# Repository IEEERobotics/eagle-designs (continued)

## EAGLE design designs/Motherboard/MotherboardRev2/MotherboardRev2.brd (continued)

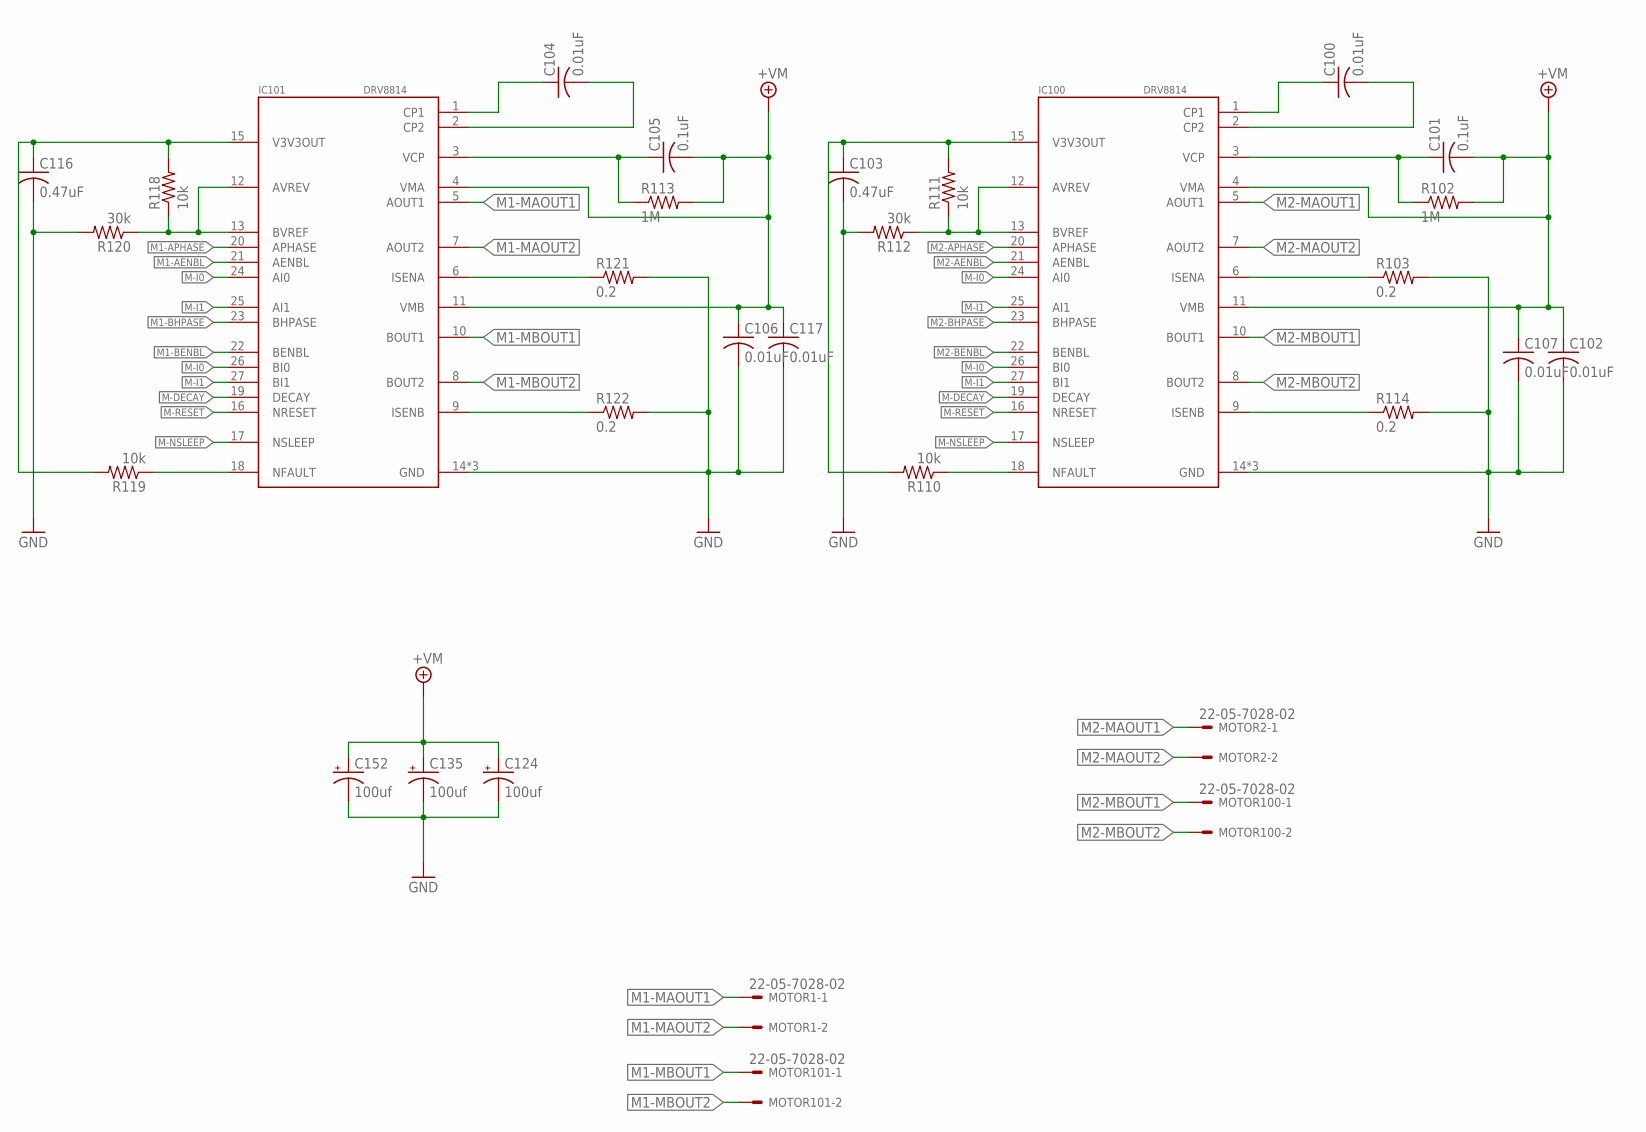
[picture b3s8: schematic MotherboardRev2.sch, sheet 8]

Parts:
C100, C102, C104, C106, C107, C117: 0.01uF; C0402
C101, C105: 0.1uF; C0402
C103, C116: 0.47uF; C0402
C124, C135, C152: 100uf; 153CLV-0605
IC100, IC101: DRV8814; TSSOP-28
MOTOR1, MOTOR2, MOTOR100, MOTOR101: 22-05-7028-02; 7395-02
R102, R113: 1M; R0402
R103, R114, R121, R122: 0.2; R0402
R110, R111, R118, R119: 10k; R0402
R112, R120: 30k; R0402

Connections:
+7V: C101.2, C102.1, C105.2, C106.1, C107.1, C117.1, C124.+, C135.+, C152.+, IC100.4 (VMA), IC100.11 (VMB), IC101.4 (VMA), IC101.11 (VMB), R102.2, R113.2; also elsewhere on the board
GND: C102.2, C103.2, C106.2, C107.2, C116.2, C117.2, C124.-, C135.-, C152.-, IC100.14 (GND), IC100.28 (GND), IC100.EXP (GND), IC101.14 (GND), IC101.28 (GND), IC101.EXP (GND), R103.2, R112.2, R114.2, R120.2, R121.2, R122.2; also elsewhere on the board
M1-AENBL: IC101.21 (AENBL); also elsewhere on the board
M1-APHASE: IC101.20 (APHASE); also elsewhere on the board
M1-BENBL: IC101.22 (BENBL); also elsewhere on the board
M1-BHPASE: IC101.23 (BHPASE); also elsewhere on the board
M1-MAOUT1: IC101.5 (AOUT1), MOTOR1.1
M1-MAOUT2: IC101.7 (AOUT2), MOTOR1.2
M1-MBOUT1: IC101.10 (BOUT1), MOTOR101.1
M1-MBOUT2: IC101.8 (BOUT2), MOTOR101.2
M2-AENBL: IC100.21 (AENBL); also elsewhere on the board
M2-APHASE: IC100.20 (APHASE); also elsewhere on the board
M2-BENBL: IC100.22 (BENBL); also elsewhere on the board
M2-BHPASE: IC100.23 (BHPASE); also elsewhere on the board
M2-MAOUT1: IC100.5 (AOUT1), MOTOR2.1
M2-MAOUT2: IC100.7 (AOUT2), MOTOR2.2
M2-MBOUT1: IC100.10 (BOUT1), MOTOR100.1
M2-MBOUT2: IC100.8 (BOUT2), MOTOR100.2
M-DECAY: IC100.19 (DECAY), IC101.19 (DECAY); also elsewhere on the board
M-I0: IC100.24 (AI0), IC100.26 (BI0), IC101.24 (AI0), IC101.26 (BI0); also elsewhere on the board
M-I1: IC100.25 (AI1), IC100.27 (BI1), IC101.25 (AI1), IC101.27 (BI1); also elsewhere on the board
M-NSLEEP: IC100.17 (NSLEEP), IC101.17 (NSLEEP); also elsewhere on the board
M-RESET: IC100.16 (NRESET), IC101.16 (NRESET); also elsewhere on the board
unnamed: C104.2, IC101.2 (CP2)
unnamed: C104.1, IC101.1 (CP1)
unnamed: C105.1, IC101.3 (VCP), R113.1
unnamed: IC101.6 (ISENA), R121.1
unnamed: IC101.9 (ISENB), R122.1
unnamed: IC101.12 (AVREV), IC101.13 (BVREF), R118.1, R120.1
unnamed: C100.2, IC100.2 (CP2)
unnamed: C100.1, IC100.1 (CP1)
unnamed: C101.1, IC100.3 (VCP), R102.1
unnamed: IC100.6 (ISENA), R103.1
unnamed: IC100.9 (ISENB), R114.1
unnamed: IC100.12 (AVREV), IC100.13 (BVREF), R111.1, R112.1
unnamed: IC101.18 (NFAULT), R119.1
unnamed: C116.1, IC101.15 (V3V3OUT), R118.2, R119.2
unnamed: IC100.18 (NFAULT), R110.1
unnamed: C103.1, IC100.15 (V3V3OUT), R110.2, R111.2

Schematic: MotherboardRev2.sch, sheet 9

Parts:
C119, C123, C131, C138, C142, C147, C150: 0.1uF; C0402
C120, C121, C122, C139, C140, C141: 0.22uF; C0402
C132, C133, C148, C149: 1nF; C0402
C134: .1uF; C0402
R125, R132, R137, R139: 0.1; R0402
R126, R127, R140, R141: 47k; R0402
R128, R129, R130, R131, R142, R143, R144, R145: 10k; R0402
STEP1, STEP2: 22-05-7048-04; 7395-04
U100, U102: DRV8811PWP; SOP65P640X120-29N

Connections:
3.3V: C131.1, C147.1, R130.1, R131.1, R142.1, R144.1, U100.10 (VCC), U102.10 (VCC); also elsewhere on the board
+7V: C119.1, C121.1, C123.1, C138.1, C140.1, C142.1, U100.15 (VMB), U100.28 (VMA), U102.15 (VMB), U102.28 (VMA); also elsewhere on the board
GND: C119.2, C120.2, C123.2, C131.2, C132.2, C133.2, C134.2, C138.2, C139.2, C142.2, C147.2, C148.2, C149.2, C150.2, R125.2, R126.2, R127.2, R128.2, R129.2, R132.2, R137.2, R139.2, R140.2, R141.2, R143.2, R145.2, U100.7 (GND_2), U100.21 (GND), U100.29 (EP), U102.7 (GND_2), U102.21 (GND), U102.29 (EP); also elsewhere on the board
M-NSLEEP: U100.27 (SLEEPN), U102.27 (SLEEPN); also elsewhere on the board
M-RESET: U100.17 (RESETN), U102.17 (RESETN); also elsewhere on the board
unnamed: R139.1, U102.14 (ISENB)
unnamed: R137.1, U102.1 (ISENA)
unnamed: C149.1, R141.1, U102.6 (RCA)
unnamed: C148.1, R140.1, U102.9 (RCB)
unnamed: C150.1, R144.2, R145.1, U102.5 (DECAY)
unnamed: R142.2, R143.1, U102.8 (VREF)
unnamed: C141.1, U102.23 (CP1)
unnamed: C141.2, U102.24 (CP2)
unnamed: C139.1, U102.20 (VGD)
unnamed: C140.2, U102.22 (VCP)
unnamed: R125.1, U100.14 (ISENB)
unnamed: R132.1, U100.1 (ISENA)
unnamed: C133.1, R127.1, U100.6 (RCA)
unnamed: C132.1, R126.1, U100.9 (RCB)
unnamed: C134.1, R129.1, R131.2, U100.5 (DECAY)
unnamed: R128.1, R130.2, U100.8 (VREF)
unnamed: C122.1, U100.23 (CP1)
unnamed: C122.2, U100.24 (CP2)
unnamed: C120.1, U100.20 (VGD)
unnamed: C121.2, U100.22 (VCP)
S1-AOUT1: STEP1.4, U102.4 (AOUT1)
S1-AOUT2: STEP1.1, U102.25 (AOUT2)
S1-BOUT1: STEP1.3, U102.11 (BOUT1)
S1-BOUT2: STEP1.2, U102.18 (BOUT2)
S1-DIR: U102.3 (DIR); also elsewhere on the board
S1-ENABLEN: U102.26 (ENABLEN); also elsewhere on the board
S1-HOME: U102.2 (HOME); also elsewhere on the board
S1-STEP: U102.19 (STEP); also elsewhere on the board
S2-AOUT1: STEP2.4, U100.4 (AOUT1)
S2-AOUT2: STEP2.1, U100.25 (AOUT2)
S2-BOUT1: STEP2.3, U100.11 (BOUT1)
S2-BOUT2: STEP2.2, U100.18 (BOUT2)
S2-DIR: U100.3 (DIR); also elsewhere on the board
S2-ENABLEN: U100.26 (ENABLEN); also elsewhere on the board
S2-HOME: U100.2 (HOME); also elsewhere on the board
S2-STEP: U100.19 (STEP); also elsewhere on the board
S-SRN: U100.16 (SRN), U102.16 (SRN); also elsewhere on the board
USM0: U100.13 (USM0), U102.13 (USM0); also elsewhere on the board
USM1: U100.12 (USM1), U102.12 (USM1); also elsewhere on the board

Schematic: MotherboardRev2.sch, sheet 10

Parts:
C1, C2, C4: 0.1uF; C0402
C3: 1uF; C0402
C19: 10uF; C0805
C115: .1uF; C0402
H1, H3: MOUNT-PAD-ROUND3.0; 3,0-PAD
IC103: PIC24FJ256GB106; TQFP64-10X10
MOTIN100, MOTIN101, MOTIN102, MOTIN103, MOTIN104: 22-05-7048-04; 7395-04
PROGRAMMING100: Jtag; MOTHER-BOARD-REV5_10-PIN-SMD
PWR_IN(2): 555X-2H; 5569-2
R116: 100; R0402
R117: 10k; R0402
SERVO_100, SERVO_101, SERVO_102: 22-05-7038-03; 7395-03
U$103: Switch3; MC32882_FINAL

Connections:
3.3V: C1.1, C2.1, C3.1, C4.1, IC103.10 (VDD), IC103.19 (AVDD), IC103.26 (VDD), IC103.38 (VDD), PROGRAMMING100.1, PROGRAMMING100.2, R117.2; also elsewhere on the board
+7V: C19.1, H1.B3,0, MOTIN100.2, MOTIN101.2, MOTIN101.3, MOTIN102.2, MOTIN103.2, MOTIN104.2, SERVO_100.2, SERVO_101.2, SERVO_102.2; also elsewhere on the board
CHANNEL_A_1: IC103.4 (RG6), MOTIN100.4
CHANNEL_A_2: IC103.22 (RB9), MOTIN102.3
CHANNEL_A_3: IC103.18 (RB7), MOTIN103.3
CHANNEL_A_4: IC103.8 (RG9), MOTIN104.3
CHANNEL_B_1: IC103.5 (RG7), MOTIN100.3
CHANNEL_B_2: IC103.21 (RB8), MOTIN102.4
CHANNEL_B_3: IC103.17 (RB6), MOTIN103.4
CHANNEL_B_4: IC103.6 (RG8), MOTIN104.4
GND: C1.2, C2.2, C3.2, C4.2, C19.2, C115.2, IC103.9 (VSS), IC103.20 (AVSS), IC103.25 (VSS), IC103.41 (VSS), MOTIN100.1, MOTIN101.1, MOTIN101.4, MOTIN102.1, MOTIN103.1, MOTIN104.1, PROGRAMMING100.9, PROGRAMMING100.10, PWR_IN(2).1, SERVO_100.3, SERVO_101.3, SERVO_102.3, U$103.P$1 (P1), U$103.P$4 (P4); also elsewhere on the board
M1-AENBL: IC103.47 (RC13); also elsewhere on the board
M1-APHASE: IC103.48 (RC14); also elsewhere on the board
M1-BENBL: IC103.46 (RD0); also elsewhere on the board
M1-BHPASE: IC103.45 (RD11); also elsewhere on the board
M2-AENBL: IC103.39 (RC12); also elsewhere on the board
M2-APHASE: IC103.43 (RD9); also elsewhere on the board
M2-BENBL: IC103.37 (RG2); also elsewhere on the board
M2-BHPASE: IC103.42 (RD8); also elsewhere on the board
M-DECAY: IC103.49 (RD1); also elsewhere on the board
M-I0: IC103.44 (RD10); also elsewhere on the board
M-I1: IC103.40 (RC15); also elsewhere on the board
M-NSLEEP: IC103.58 (RF0); also elsewhere on the board
M-RESET: IC103.60 (RE0); also elsewhere on the board
M_MCLR: C115.1, PROGRAMMING100.7, PROGRAMMING100.8, R116.2, R117.1, U$103.P$2 (P2), U$103.P$3 (P3)
M_MCLR': IC103.7 (!MCLR), R116.1
M_PGC1: IC103.15 (RB1), PROGRAMMING100.3, PROGRAMMING100.4
M_PGD1: IC103.16 (RB0), PROGRAMMING100.5, PROGRAMMING100.6
OC1': IC103.33 (RF3), SERVO_102.1
OC2': IC103.32 (RF5), SERVO_101.1
OC3': IC103.31 (RF4), SERVO_100.1
S1-DIR: IC103.64 (RE4); also elsewhere on the board
S1-ENABLEN: IC103.55 (RD7); also elsewhere on the board
S1-HOME: IC103.63 (RE3); also elsewhere on the board
S1-STEP: IC103.53 (RD5); also elsewhere on the board
S2-DIR: IC103.54 (RD6); also elsewhere on the board
S2-ENABLEN: IC103.51 (RD3); also elsewhere on the board
S2-HOME: IC103.52 (RD4); also elsewhere on the board
S2-STEP: IC103.50 (RD2); also elsewhere on the board
S-SRN: IC103.59 (RF1); also elsewhere on the board
SCL: IC103.2 (RE6); also elsewhere on the board
SDA: IC103.3 (RE7); also elsewhere on the board
USM0: IC103.62 (RE2); also elsewhere on the board
USM1: IC103.61 (RE1); also elsewhere on the board
VCC: PWR_IN(2).2; also elsewhere on the board
VDDCORE: IC103.56 (VDDCORE)

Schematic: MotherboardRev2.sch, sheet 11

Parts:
C6, C7, C8, C130: 4.7uF; 1206
C118: 10nF; 0805
C146: 330uF; SM_RADIAL_10AMM
D103: PDS760-13; POWERDI5
L103: WE-HCC-7443331000_1090; WE-HCC_1090
LED1, LED104: LEDCHIP-LED0603; CHIP-LED0603
POWER_ON: LEDCHIP-LED0603; CHIP-LED0603
R2, R101, R123, R146: 10k; R0402
R124: 2.55k; R0402
U$1: LOGO
U$107: TPS5450DDAR; R-PDSO-G8

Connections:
+7V: C146.1 (+), L103.2, R2.2, R123.2, R146.2; also elsewhere on the board
BOOT_VM: C118.1, U$107.1 (BOOT)
GND: C6.1, C7.1, C8.1, C130.1, C146.2 (-), D103.1 (A_2), LED1.C, LED104.C, POWER_ON.C, R124.1, U$107.6 (GND_2), U$107.9 (PWPD); also elsewhere on the board
unnamed: LED104.A, R146.1
unnamed: POWER_ON.A, R101.1
unnamed: LED1.A, R2.1
PH_VM: C118.2, D103.3 (K), L103.1, U$107.8 (PH)
VCC: C6.2, C7.2, C8.2, C130.2, R101.2, U$107.7 (VIN); also elsewhere on the board
VSNS_VM: R123.1, R124.2, U$107.4 (VSNS)

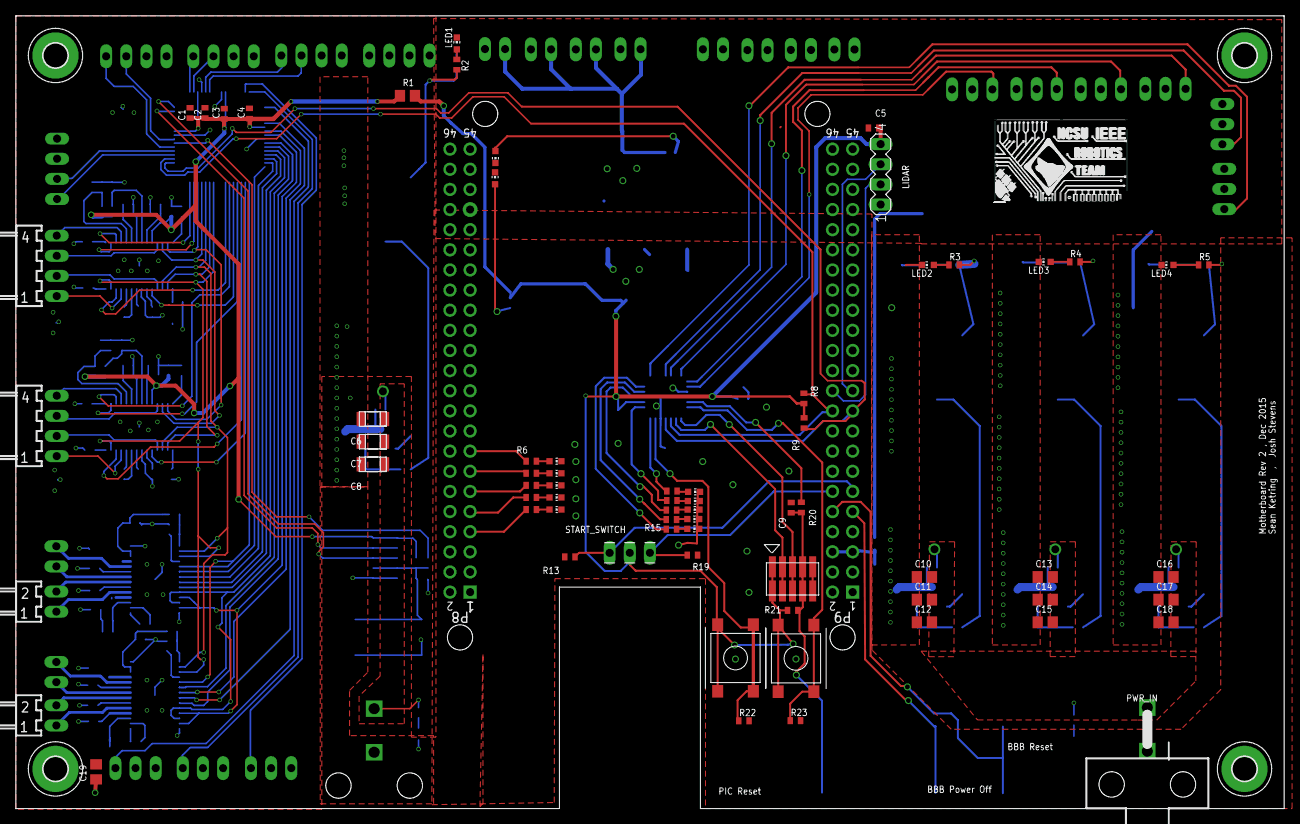
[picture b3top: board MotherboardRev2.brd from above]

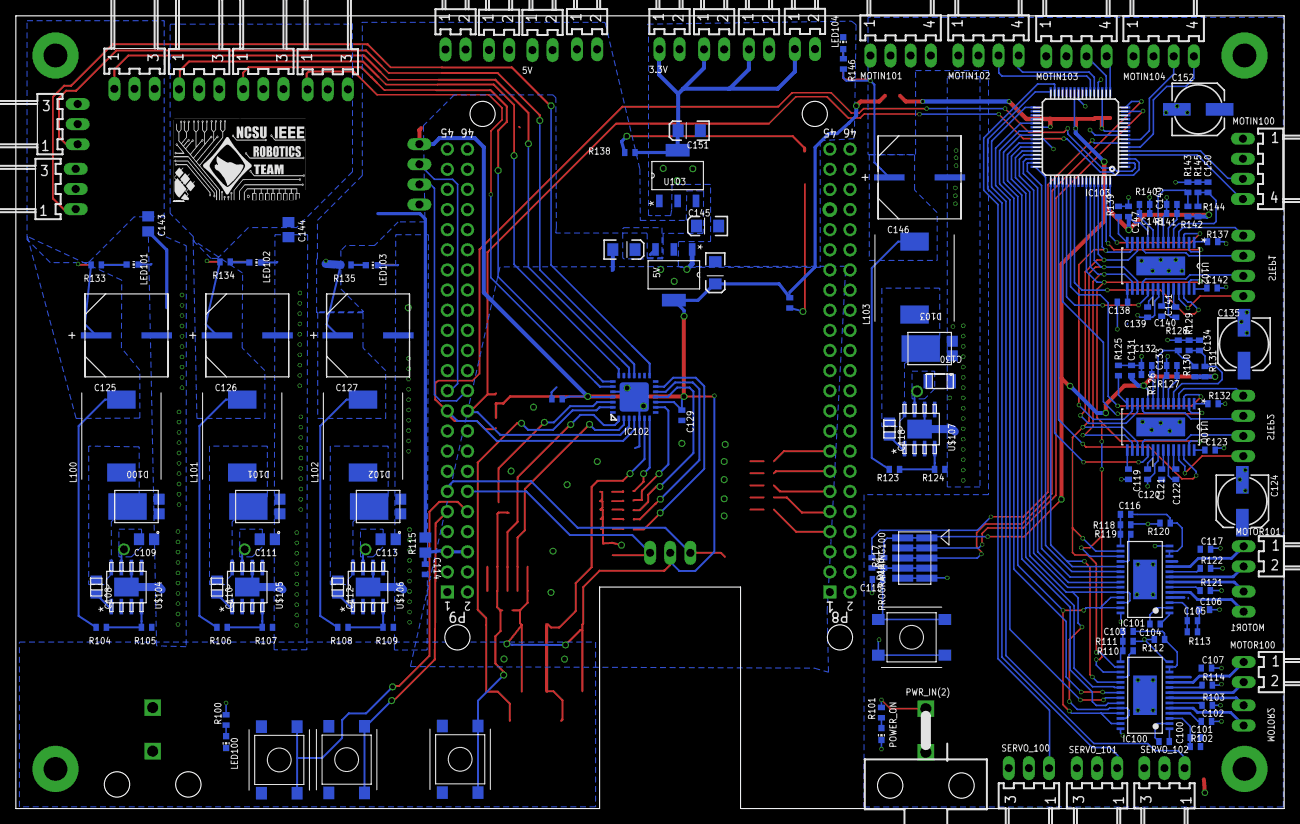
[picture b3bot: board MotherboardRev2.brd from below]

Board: 2 copper layers, 160.0 x 100.0 mm, 232 parts (157 on the bottom side), 164 nets.

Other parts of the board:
U$2, U$108: LOGO

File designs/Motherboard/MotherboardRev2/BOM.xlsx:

Part | Value | Device
3.3V | 22-05-7028-02 | 7395-02
3.3V(2) | 22-05-7028-02 | 7395-02
3.3V(2)1 | 22-05-7028-02 | 7395-02
3.3V1 | 22-05-7028-02 | 7395-02
5V | 22-05-7028-02 | 7395-02
5V(2) | 22-05-7028-02 | 7395-02
5V(2)1 | 22-05-7028-02 | 7395-02
5V1 | 22-05-7028-02 | 7395-02
C1 | 0.1uF | C-USC0402
C2 | 0.1uF | C-USC0402
C3 | 1uF | C-USC0402
C4 | 0.1uF | C-USC0402
C5 | 4.7uF | C-USC0402
C6 | 4.7uF | GRM31CR71H475KA12L
C7 | 4.7uF | GRM31CR71H475KA12L
C8 | 4.7uF | GRM31CR71H475KA12L
C9 | .1uF | C-USC0402
C10 | 4.7uF | C-USC0805
C11 | 4.7uF | C-USC0805
C12 | 4.7uF | C-USC0805
C13 | 4.7uF | C-USC0805
C14 | 4.7uF | C-USC0805
C15 | 4.7uF | C-USC0805
C16 | 4.7uF | C-USC0805
C17 | 4.7uF | C-USC0805
C18 | 4.7uF | C-USC0805
C19 | 10uF | C-USC0805
C100 | 0.01uF | C-USC0402
C101 | 0.1uF | C-USC0402
C102 | 0.01uF | C-USC0402
C103 | 0.47uF | C-USC0402
C104 | 0.01uF | C-USC0402
C105 | 0.1uF | C-USC0402
C106 | 0.01uF | C-USC0402
C107 | 0.01uF | C-USC0402
C108 | 10nF | C0805C103K5RACTU
C109 | 4.7uF | C-USC0805
C110 | 10nF | C0805C103K5RACTU
C111 | 4.7uF | C-USC0805
C112 | 10nF | C0805C103K5RACTU
C113 | 4.7uF | C-USC0805
C114 | .1uF | C-USC0402
C115 | .1uF | C-USC0402
C116 | 0.47uF | C-USC0402
C117 | 0.01uF | C-USC0402
C118 | 10nF | C0805C103K5RACTU
C119 | 0.1uF | C-USC0402
C120 | 0.22uF | C-USC0402
C121 | 0.22uF | C-USC0402
C122 | 0.22uF | C-USC0402
C123 | 0.1uF | C-USC0402
C124 | 100uf | CPOL-US153CLV-0605
C125 | 330uF | 10SVP330MX
C126 | 330uF | 10SVP330MX
C127 | 330uF | 10SVP330MX
C128 | .1uF | C-USC0402
C129 | .1uF | C-USC0402
C130 | 4.7uF | GRM31CR71H475KA12L
C131 | 0.1uF | C-USC0402
C132 | 1nF | C-USC0402
C133 | 1nF | C-USC0402
C134 | .1uF | C-USC0402
C135 | 100uf | CPOL-US153CLV-0605
C136 | 10uF | 10UF-16V-10%(TANT)
C137 | 10uF | 10UF-16V-10%(TANT)
C138 | 0.1uF | C-USC0402
C139 | 0.22uF | C-USC0402
C140 | 0.22uF | C-USC0402
C141 | 0.22uF | C-USC0402
C142 | 0.1uF | C-USC0402
C143 | 10uF | C-USC0805
C144 | 10uF | C-USC0805
C145 | 10uF | 10UF-16V-10%(TANT)
C146 | 330uF | 10SVP330MX
C147 | 0.1uF | C-USC0402
C148 | 1nF | C-USC0402
C149 | 1nF | C-USC0402
C150 | 0.1uF | C-USC0402
C151 | 10uF | 10UF-16V-10%(TANT)
C152 | 100uf | CPOL-US153CLV-0605
D1 | 3_3V_PWR | LEDCHIP-LED0603
D2 | 3_3V_PWR | LEDCHIP-LED0603
D100 | PDS760-13 | PDS760-13
D101 | PDS760-13 | PDS760-13
D102 | PDS760-13 | PDS760-13
D103 | PDS760-13 | PDS760-13
H1 | MOUNT-PAD-ROUND3.0 | MOUNT-PAD-ROUND3.0
H2 | MOUNT-PAD-ROUND3.0 | MOUNT-PAD-ROUND3.0
H3 | MOUNT-PAD-ROUND3.0 | MOUNT-PAD-ROUND3.0
H4 | MOUNT-PAD-ROUND3.0 | MOUNT-PAD-ROUND3.0
IC100 | DRV8814 | DRV8818PWPR
IC101 | DRV8814 | DRV8818PWPR
IC102 | PIC24FJ64GB202 | PIC18F26J53ML
IC103 | PIC24FJ256GB106 | PIC24FJ256GB106
L100 | WE-HCC-7443331000_1090 | WE-HCC_1090
L101 | WE-HCC-7443331000_1090 | WE-HCC_1090
L102 | WE-HCC-7443331000_1090 | WE-HCC_1090
L103 | WE-HCC-7443331000_1090 | WE-HCC_1090
LED1 | LEDCHIP-LED0603 | CHIP-LED0603
LED2 | LEDCHIP-LED0603 | CHIP-LED0603
LED3 | LEDCHIP-LED0603 | CHIP-LED0603
LED4 | LEDCHIP-LED0603 | CHIP-LED0603
LED5 | LEDCHIP-LED0603 | CHIP-LED0603
LED6 | LEDCHIP-LED0603 | CHIP-LED0603
LED7 | LEDCHIP-LED0603 | CHIP-LED0603
LED8 | LEDCHIP-LED0603 | CHIP-LED0603
LED9 | LEDCHIP-LED0603 | CHIP-LED0603
LED10 | LEDCHIP-LED0603 | CHIP-LED0603
LED11 | LEDCHIP-LED0603 | CHIP-LED0603
LED12 | LEDCHIP-LED0603 | CHIP-LED0603
LED13 | LEDCHIP-LED0603 | CHIP-LED0603
LED14 | LEDCHIP-LED0603 | CHIP-LED0603
LED100 | LEDCHIP-LED0603 | CHIP-LED0603
LED101 | LEDCHIP-LED0603 | CHIP-LED0603
LED102 | LEDCHIP-LED0603 | CHIP-LED0603
LED103 | LEDCHIP-LED0603 | CHIP-LED0603
LED104 | LEDCHIP-LED0603 | CHIP-LED0603
LIDAR | MA04-1 | MA04-1
MOTIN100 | 22-05-7048-04 | 22-05-7048-04
MOTIN101 | 22-05-7048-04 | 22-05-7048-04
MOTIN102 | 22-05-7048-04 | 22-05-7048-04
MOTIN103 | 22-05-7048-04 | 22-05-7048-04
MOTIN104 | 22-05-7048-04 | 22-05-7048-04
MOTOR1 | 22-05-7028-02 | 22-05-7028-02
MOTOR2 | 22-05-7028-02 | 22-05-7028-02
MOTOR100 | 22-05-7028-02 | 22-05-7028-02
MOTOR101 | 22-05-7028-02 | 22-05-7028-02
POWER_ON | LEDCHIP-LED0603 | CHIP-LED0603
PROGRAMMING | Jtag | MOTHER-BOARD-REV5_PIN-CONNECTOR74089
PROGRAMMING100 | Jtag | MOTHER-BOARD-REV5_PIN-CONNECTOR74089
PWR_IN | 555X-2H | 5569-2
PWR_IN(2) | 555X-2H | 5569-2
R1 | 0 | R-US_R0805
R2 | 10k | R-US_R0402
R3 | 10k | R-US_R0402
R4 | 10k | R-US_R0402
R5 | 10k | R-US_R0402
R6 | 1K | R-US_R0402
R7 | 1K | R-US_R0402
R8 | 4.7K | R-US_R0402
R9 | 4.7K | R-US_R0402
R10 | 1K | R-US_R0402
R11 | 1K | R-US_R0402
R12 | 1K | R-US_R0402
R13 | 10K | R-US_R0402
R14 | 330 | R-US_R0402
R15 | 330 | R-US_R0402
R16 | 330 | R-US_R0402
R17 | 330 | R-US_R0402
R18 | 330 | R-US_R0402
R19 | 10K | R-US_R0402
R20 | 100 | R-US_R0402
R21 | 10k | R-US_R0402
R22 | 10K | R-US_R0402
R23 | 10K | R-US_R0402
R100 | 10k | R-US_R0402
R101 | 10k | R-US_R0402
R102 | 1M | R-US_R0402
R103 | 0.2 | R-US_R0402
R104 | 10k | R-US_R0402
R105 | 2.55k | R-US_R0402
R106 | 10k | R-US_R0402
R107 | 2.55k | R-US_R0402
R108 | 10k | R-US_R0402
R109 | 3.23K | R-US_R0402
R110 | 10k | R-US_R0402
R111 | 10k | R-US_R0402
R112 | 30k | R-US_R0402
R113 | 1M | R-US_R0402
R114 | 0.2 | R-US_R0402
R115 | 0 | ohm
R116 | 100 | R-US_R0402
R117 | 10k | R-US_R0402
R118 | 10k | R-US_R0402
R119 | 10k | R-US_R0402
R120 | 30k | R-US_R0402
R121 | 0.2 | R-US_R0402
R122 | 0.2 | R-US_R0402
R123 | 10k | R-US_R0402
R124 | 2.55k | R-US_R0402
R125 | 0.1 | R-US_R0402
R126 | 47k | R-US_R0402
R127 | 47k | R-US_R0402
R128 | 10k | R-US_R0402
R129 | 10k | R-US_R0402
R130 | 10k | R-US_R0402
R131 | 10k | R-US_R0402
R132 | 0.1 | R-US_R0402
R133 | 10k | R-US_R0402
R134 | 10k | R-US_R0402
R135 | 10k | R-US_R0402
R136 | 330 | R-US_R0805W
R137 | 0.1 | R-US_R0402
R138 | 330 | R-US_R0805W
R139 | 0.1 | R-US_R0402
R140 | 47k | R-US_R0402
R141 | 47k | R-US_R0402
R142 | 10k | R-US_R0402
R143 | 10k | R-US_R0402
R144 | 10k | R-US_R0402
R145 | 10k | R-US_R0402
R146 | 10k | R-US_R0402
SERVO_100 | 22-05-7038-03 | 7395-03
SERVO_101 | 22-05-7038-03 | 7395-03
SERVO_102 | 22-05-7038-03 | 7395-03
SERVO_103 | 22-05-7038-03 | 7395-03
SERVO_104 | 22-05-7038-03 | 7395-03
SERVO_105 | 22-05-7038-03 | 7395-03
SERVO_106 | 22-05-7038-03 | 7395-03
SERVO_107 | 22-05-7038-03 | 7395-03
SERVO_108 | 22-05-7038-03 | 7395-03
START_SWITCH | MA03-1 | MA03-1
STEP1 | 22-05-7048-04 | 22-05-7048-04
STEP2 | 22-05-7048-04 | 22-05-7048-04
U$1 | LOGO | LOGO
U$3 | Switch2 | MC32882_SW
U$4 | Switch1 | MC32882_SW
U$5 | BEAGLE_BONE_BLACK_CAPE | BEAGLE_BONE_BLACK_CAPE
U$100 | Switch1 | MC32882_SW
U$101 | Switch1 | MC32882_SW
U$102 | Switch3 | MC32882_SW
U$103 | Switch3 | MC32882_SW
U$104 | TPS5450DDAR | TPS5450DDAR
U$105 | TPS5450DDAR | TPS5450DDAR
U$106 | TPS5450DDAR | TPS5450DDAR
U$107 | TPS5450DDAR | TPS5450DDAR
U100 | DRV8811PWP | DRV8811PWP
U101 | LMS8117AMP-3.3 | LMS8117AMP-3.3
U102 | DRV8811PWP | DRV8811PWP
U103 | LMS8117AMP-3.3 | LMS8117AMP-3.3

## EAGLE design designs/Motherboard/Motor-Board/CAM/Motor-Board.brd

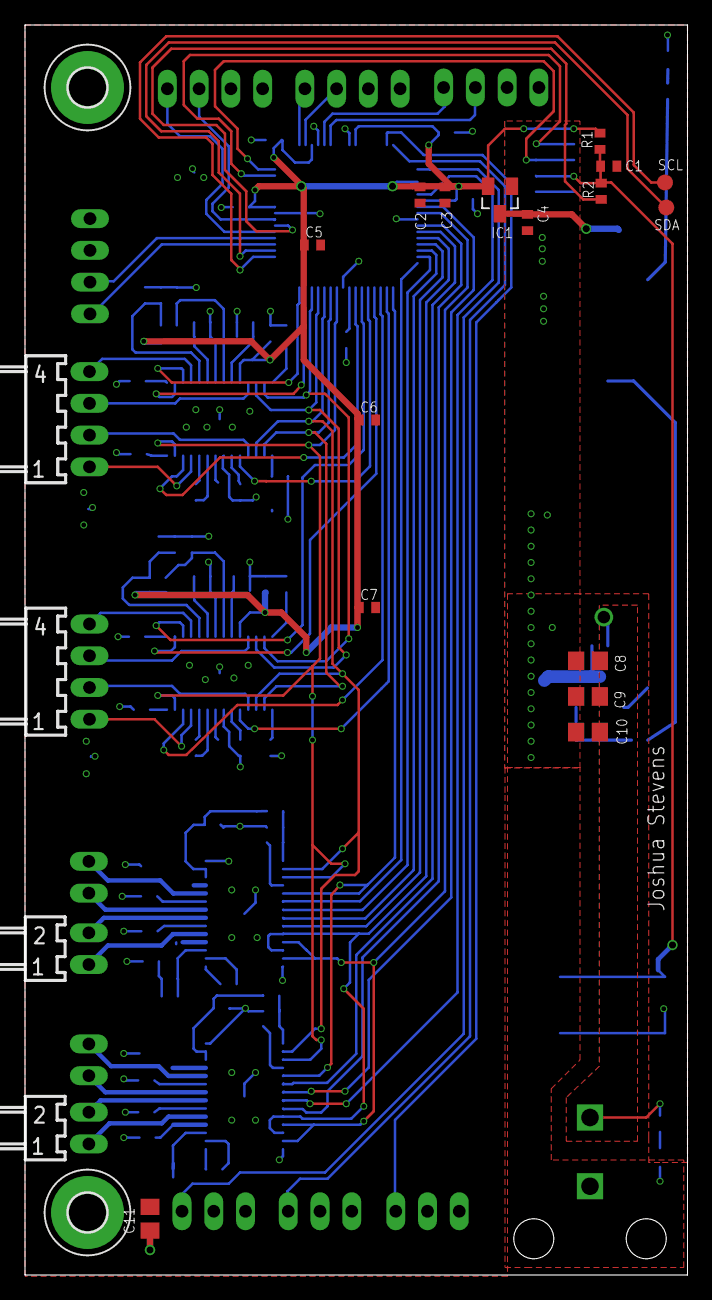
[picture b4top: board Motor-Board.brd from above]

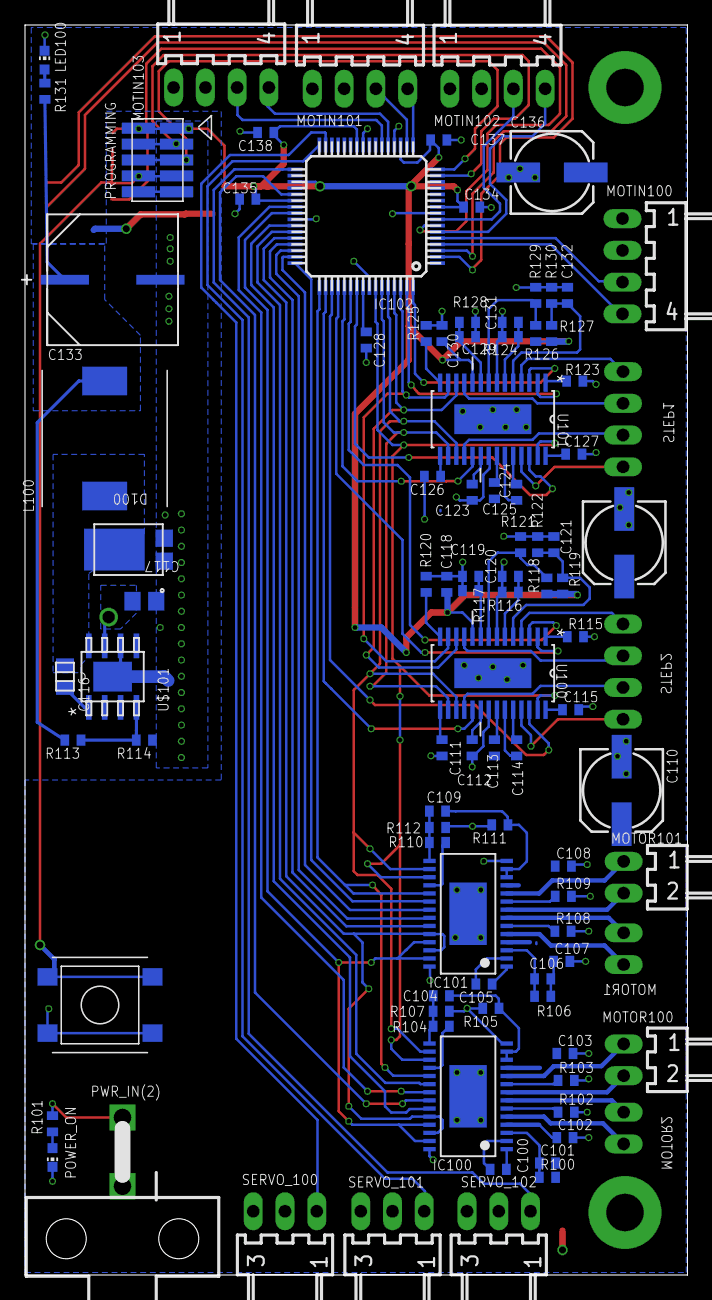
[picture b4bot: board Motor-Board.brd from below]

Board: 2 copper layers, 53.0 x 100.0 mm, 115 parts (93 on the bottom side), 103 nets.

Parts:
C1, C121, C138: .1uF; C0402
C2, C128: 10uF; C0402
C3, C4, C5, C6, C7, C101, C106, C111, C115, C118, C126, C127, C130, C132, C134, C135, C137: 0.1uF; C0402
C8, C9, C10, C117: 4.7uF; C0805
C11: 10uF; C0805
C100, C102, C103, C105, C107, C108: 0.01uF; C0402
C104, C109: 0.47uF; C0402
C110, C122, C136: 153CLV-0605
C112, C113, C114, C123, C124, C125: 0.22uF; C0402
C116: 10nF; 0805
C119, C120, C129, C131: 1nF; C0402
C133: 330uF; SM_RADIAL_10AMM
D100: PDS760-13; POWERDI5
H1, H2: MOUNT-PAD-ROUND3.0; 3,0-PAD
IC1: MCP1703CB; SOT23
IC100, IC101: DRV8814; TSSOP-28
IC102: PIC24FJ256GB106; TQFP64-10X10
L100: WE-HCC_1090
LED100: CHIP-LED0603
MOTIN100, MOTIN101, MOTIN102, MOTIN103: 22-05-7048-04; 7395-04
MOTOR1, MOTOR2, MOTOR100, MOTOR101: 22-05-7028-02; 7395-02
POWER_ON: CHIP-LED0603
PROGRAMMING: Jtag; MOTHER-BOARD-REV5_10-PIN-SMD
PWR_IN(2): 5569-2
R1, R101, R104, R107, R110, R112, R113, R118, R119, R121, R122, R126, R127, R129, R130, R131: 10k; R0402
R2: 100; R0402
R100, R106: 1M; R0402
R102, R103, R108, R109: 0.2; R0402
R105, R111: 30k; R0402
R114: R0402
R115, R120, R123, R125: 0.1; R0402
R116, R117, R124, R128: 47k; R0402
SCL: PTR1B1,27; B1,27
SDA: PTR1B1,27; B1,27
SERVO_100, SERVO_101, SERVO_102: 7395-03
STEP1, STEP2: 22-05-7048-04; 7395-04
U100, U101: DRV8811PWP; SOP65P640X120-29N
U$100: Switch3; MC32882_FINAL
U$101: TPS5450DDAR; R-PDSO-G8

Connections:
+3V3: C2.1, C3.1, C5.1, C6.1, C7.1, C118.1, C130.1, C134.1, C135.1, C137.1, C138.1, IC1.2, IC102.10, IC102.19, IC102.26, IC102.35, IC102.38, PROGRAMMING.1, PROGRAMMING.2, R1.2, R118.1, R119.1, R126.1, R127.1, U100.10, U101.10
+7V: C4.1, C11.1, C101.2, C102.1, C103.1, C106.2, C107.1, C108.1, C110.+, C111.1, C113.1, C115.1, C122.+, C125.1, C126.1, C127.1, C133.1, C136.+, IC1.3, IC100.4, IC100.11, IC101.4, IC101.11, L100.2, MOTIN100.2, MOTIN101.2, MOTIN102.2, MOTIN103.2, R100.2, R106.2, R113.2, R131.2, SERVO_100.2, SERVO_101.2, SERVO_102.2, U100.15, U100.28, U101.15, U101.28
BOOT_VM: C116.1, U$101.1
CHANNEL_A_1: IC102.4, MOTIN100.4
CHANNEL_A_2: IC102.22, MOTIN103.3
CHANNEL_A_3: IC102.18, MOTIN101.3
CHANNEL_A_4: IC102.8, MOTIN102.3
CHANNEL_B_1: IC102.5, MOTIN100.3
CHANNEL_B_2: IC102.21, MOTIN103.4
CHANNEL_B_3: IC102.17, MOTIN101.4
CHANNEL_B_4: IC102.6, MOTIN102.4
GND: C1.2, C2.2, C3.2, C4.2, C5.2, C6.2, C7.2, C8.1, C9.1, C10.1, C11.2, C102.2, C103.2, C104.2, C107.2, C108.2, C109.2, C110.-, C111.2, C112.2, C115.2, C117.1, C118.2, C119.2, C120.2, C121.2, C122.-, C123.2, C126.2, C127.2, C128.2, C129.2, C130.2, C131.2, C132.2, C133.2, C134.2, C135.2, C136.-, C137.2, C138.2, D100.1, IC1.1, IC100.14, IC100.28, IC100.EXP, IC101.14, IC101.28, IC101.EXP, IC102.9, IC102.20, IC102.25, IC102.41, IC102.57, LED100.C, MOTIN100.1, MOTIN101.1, MOTIN102.1, MOTIN103.1, POWER_ON.C, PROGRAMMING.9, PROGRAMMING.10, PWR_IN(2).1, R102.2, R103.2, R105.2, R108.2, R109.2, R111.2, R114.1, R115.2, R116.2, R117.2, R120.2, R121.2, R122.2, R123.2, R124.2, R125.2, R128.2, R129.2, R130.2, SERVO_100.3, SERVO_101.3, SERVO_102.3, U100.7, U100.21, U100.29, U101.7, U101.21, U101.29, U$100.P$1, U$100.P$4, U$101.6, U$101.9
M1-AENBL: IC101.21, IC102.47
M1-APHASE: IC101.20, IC102.48
M1-BENBL: IC101.22, IC102.46
M1-BHPASE: IC101.23, IC102.45
M1-MAOUT1: IC101.5, MOTOR1.1
M1-MAOUT2: IC101.7, MOTOR1.2
M1-MBOUT1: IC101.10, MOTOR101.1
M1-MBOUT2: IC101.8, MOTOR101.2
M2-AENBL: IC100.21, IC102.39
M2-APHASE: IC100.20, IC102.43
M2-BENBL: IC100.22, IC102.37
M2-BHPASE: IC100.23, IC102.42
M2-MAOUT1: IC100.5, MOTOR2.1
M2-MAOUT2: IC100.7, MOTOR2.2
M2-MBOUT1: IC100.10, MOTOR100.1
M2-MBOUT2: IC100.8, MOTOR100.2
M-DECAY: IC100.19, IC101.19, IC102.49
M-I0: IC100.24, IC100.26, IC101.24, IC101.26, IC102.44
M-I1: IC100.25, IC100.27, IC101.25, IC101.27, IC102.40
M-NSLEEP: IC100.17, IC101.17, IC102.58, U100.27, U101.27
M-RESET: IC100.16, IC101.16, IC102.60, U100.17, U101.17
M_MCLR: C1.1, PROGRAMMING.7, PROGRAMMING.8, R1.1, R2.2, U$100.P$2, U$100.P$3
M_MCLR': IC102.7, R2.1
M_PGC1: IC102.15, PROGRAMMING.3, PROGRAMMING.4
M_PGD1: IC102.16, PROGRAMMING.5, PROGRAMMING.6
unnamed: C105.2, IC101.2
unnamed: C105.1, IC101.1
unnamed: C106.1, IC101.3, R106.1
unnamed: IC101.6, R108.1
unnamed: C100.2, IC100.2
unnamed: C100.1, IC100.1
unnamed: C101.1, IC100.3, R100.1
unnamed: IC100.6, R102.1
unnamed: IC100.9, R103.1
unnamed: IC101.9, R109.1
unnamed: IC100.12, IC100.13, R105.1, R107.1
unnamed: IC101.12, IC101.13, R111.1, R112.1
unnamed: R125.1, U101.14
unnamed: R123.1, U101.1
unnamed: R120.1, U100.14
unnamed: R115.1, U100.1
unnamed: C120.1, R116.1, U100.6
unnamed: C131.1, R124.1, U101.6
unnamed: C129.1, R128.1, U101.9
unnamed: C119.1, R117.1, U100.9
unnamed: C121.1, R119.2, R122.1, U100.5
unnamed: R118.2, R121.1, U100.8
unnamed: C114.1, U100.23
unnamed: C114.2, U100.24
unnamed: LED100.A, R131.1
unnamed: C132.1, R127.2, R130.1, U101.5
unnamed: C112.1, U100.20
unnamed: C113.2, U100.22
unnamed: C109.1, IC101.15, R110.2, R112.2
unnamed: R126.2, R129.1, U101.8
unnamed: IC101.18, R110.1
unnamed: C124.1, U101.23
unnamed: C124.2, U101.24
unnamed: C123.1, U101.20
unnamed: IC100.18, R104.1
unnamed: C125.2, U101.22
unnamed: C104.1, IC100.15, R104.2, R107.2
unnamed: POWER_ON.A, R101.1
unnamed: C128.1, IC102.56
OC1: IC102.33, SERVO_102.1
OC2: IC102.32, SERVO_101.1
OC3: IC102.31, SERVO_100.1
PH_VM: C116.2, D100.3, L100.1, U$101.8
S1-AOUT1: STEP1.4, U101.4
S1-AOUT2: STEP1.1, U101.25
S1-BOUT1: STEP1.3, U101.11
S1-BOUT2: STEP1.2, U101.18
S1-DIR: IC102.64, U101.3
S1-ENABLEN: IC102.55, U101.26
S1-HOME: IC102.63, U101.2
S1-STEP: IC102.53, U101.19
S2-AOUT1: STEP2.4, U100.4
S2-AOUT2: STEP2.1, U100.25
S2-BOUT1: STEP2.3, U100.11
S2-BOUT2: STEP2.2, U100.18
S2-DIR: IC102.54, U100.3
S2-ENABLEN: IC102.51, U100.26
S2-HOME: IC102.52, U100.2
S2-STEP: IC102.50, U100.19
S-SRN: IC102.59, U100.16, U101.16
SCL: IC102.2, SCL.TP
SDA: IC102.3, SDA.TP
USM0: IC102.62, U100.13, U101.13
USM1: IC102.61, U100.12, U101.12
VCC: C8.2, C9.2, C10.2, C117.2, PWR_IN(2).2, R101.2, U$101.7
VSNS_VM: R113.1, R114.2, U$101.4
